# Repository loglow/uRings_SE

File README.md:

# µRings SE (uRings, microRings) Eurorack [Rev D]

## 8HP Eurorack module | Resonator

[μRings SE](http://urings-se.com) is a resonator, transforming unpitched external excitation signals into pitched sounds by modeling the vibrations of bars, tubes, and strings.

This re-engineered Eurorack module updates and simplifies the classic [Mutable Instruments Rings](https://mutable-instruments.net/modules/rings/) design by miniaturizing the module from 14HP to 8HP and redesigning the front panel layout without eliminating any original functionality.

Fully compatible with upstream Rings firmware. Includes power cable, mounting hardware, and a one-year warranty. Designed and built with care by [Tall Dog Electronics](http://tall-dog.com) in Western Massachusetts. Licensed [CC BY-SA 4.0](https://creativecommons.org/licenses/by-sa/4.0/) open source hardware.

- **Height:** 3U (128.5 mm)
- **Width:** 8HP (40.3 mm)
- **Depth:** 43 mm (with power)
- **+12V:** 120 mA (average)
- **-12V:** 5 mA (average)

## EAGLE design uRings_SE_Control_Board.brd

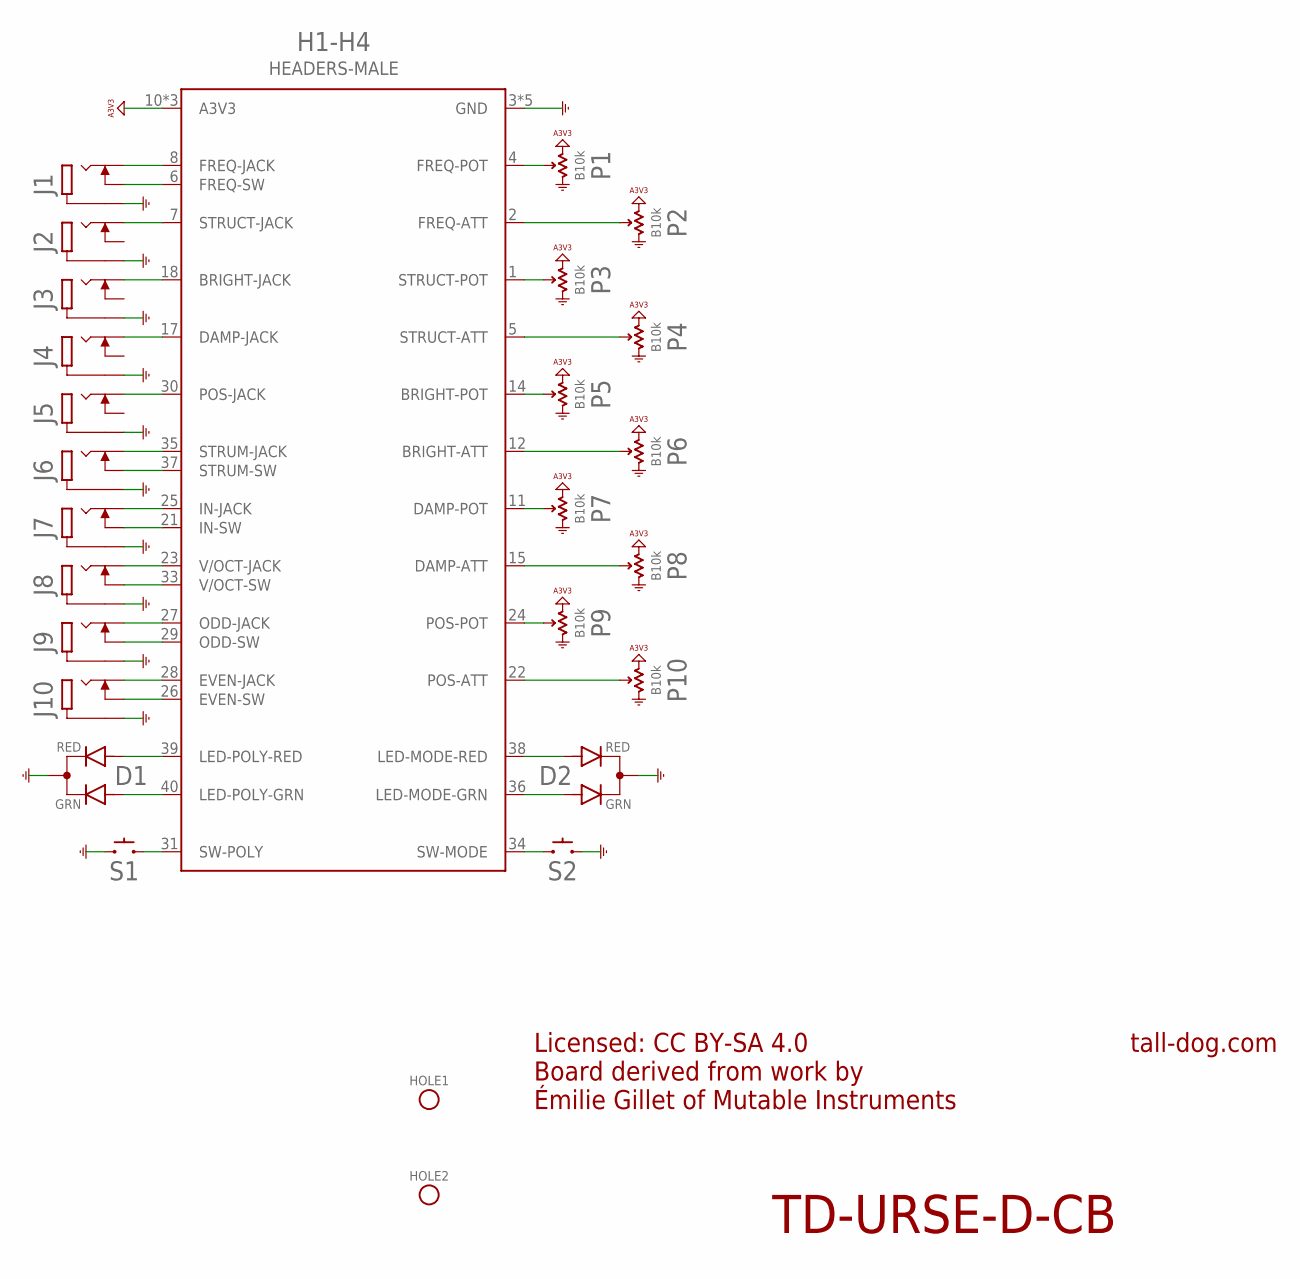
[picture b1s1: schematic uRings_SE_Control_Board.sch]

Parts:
D1, D2: LED-DUAL; LED-T1-3
H1-H4: HEADERS-MALE
HOLE1, HOLE2: HOLE; M2.5-HOLE
J1, J2, J3, J4, J5, J6, J7, J8, J9, J10: JACK
P1, P2, P3, P4, P5, P6, P7, P8, P9, P10: B10k; POT
S1, S2: SPST; TL1105

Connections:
A3V3: H1-H4.10 (A3V3), H1-H4.16 (A3V3), H1-H4.20 (A3V3), P1.P$1 (E), P2.P$1 (E), P3.P$1 (E), P4.P$1 (E), P5.P$1 (E), P6.P$1 (E), P7.P$1 (E), P8.P$1 (E), P9.P$1 (E), P10.P$1 (E)
BRIGHT-ATT: H1-H4.12 (BRIGHT-ATT), P6.P$2 (S)
BRIGHT-JACK: H1-H4.18 (BRIGHT-JACK), J3.P3 (3)
BRIGHT-POT: H1-H4.14 (BRIGHT-POT), P5.P$2 (S)
DAMP-ATT: H1-H4.15 (DAMP-ATT), P8.P$2 (S)
DAMP-JACK: H1-H4.17 (DAMP-JACK), J4.P3 (3)
DAMP-POT: H1-H4.11 (DAMP-POT), P7.P$2 (S)
EVEN-JACK: H1-H4.28 (EVEN-JACK), J10.P3 (3)
EVEN-SW: H1-H4.26 (EVEN-SW), J10.P2 (2)
FREQ-ATT: H1-H4.2 (FREQ-ATT), P2.P$2 (S)
FREQ-JACK: H1-H4.8 (FREQ-JACK), J1.P3 (3)
FREQ-POT: H1-H4.4 (FREQ-POT), P1.P$2 (S)
FREQ-SW: H1-H4.6 (FREQ-SW), J1.P2 (2)
GND: D1.2 (C), D2.2 (C), H1-H4.3 (GND), H1-H4.9 (GND), H1-H4.13 (GND), H1-H4.19 (GND), H1-H4.32 (GND), J1.P1 (1), J2.P1 (1), J3.P1 (1), J4.P1 (1), J5.P1 (1), J6.P1 (1), J7.P1 (1), J8.P1 (1), J9.P1 (1), J10.P1 (1), P1.P$3 (A), P2.P$3 (A), P3.P$3 (A), P4.P$3 (A), P5.P$3 (A), P6.P$3 (A), P7.P$3 (A), P8.P$3 (A), P9.P$3 (A), P10.P$3 (A), S1.1, S1.2 (1), S2.1, S2.2 (1)
IN-JACK: H1-H4.25 (IN-JACK), J7.P3 (3)
IN-SW: H1-H4.21 (IN-SW), J7.P2 (2)
LED-MODE-GRN: D2.3 (GRN), H1-H4.36 (LED-MODE-GRN)
LED-MODE-RED: D2.1 (RED), H1-H4.38 (LED-MODE-RED)
LED-POLY-GRN: D1.3 (GRN), H1-H4.40 (LED-POLY-GRN)
LED-POLY-RED: D1.1 (RED), H1-H4.39 (LED-POLY-RED)
ODD-JACK: H1-H4.27 (ODD-JACK), J9.P3 (3)
ODD-SW: H1-H4.29 (ODD-SW), J9.P2 (2)
POS-ATT: H1-H4.22 (POS-ATT), P10.P$2 (S)
POS-JACK: H1-H4.30 (POS-JACK), J5.P3 (3)
POS-POT: H1-H4.24 (POS-POT), P9.P$2 (S)
STRUCT-ATT: H1-H4.5 (STRUCT-ATT), P4.P$2 (S)
STRUCT-JACK: H1-H4.7 (STRUCT-JACK), J2.P3 (3)
STRUCT-POT: H1-H4.1 (STRUCT-POT), P3.P$2 (S)
STRUM-JACK: H1-H4.35 (STRUM-JACK), J6.P3 (3)
STRUM-SW: H1-H4.37 (STRUM-SW), J6.P2 (2)
SW-MODE: H1-H4.34 (SW-MODE), S2.3 (2), S2.4 (2)
SW-POLY: H1-H4.31 (SW-POLY), S1.3 (2), S1.4 (2)
V/OCT-JACK: H1-H4.23 (V/OCT-JACK), J8.P3 (3)
V/OCT-SW: H1-H4.33 (V/OCT-SW), J8.P2 (2)

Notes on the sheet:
Licensed: CC BY-SA 4.0 Board derived from work by Émilie Gillet of Mutable Instruments
tall-dog.com
TD-URSE-D-CB

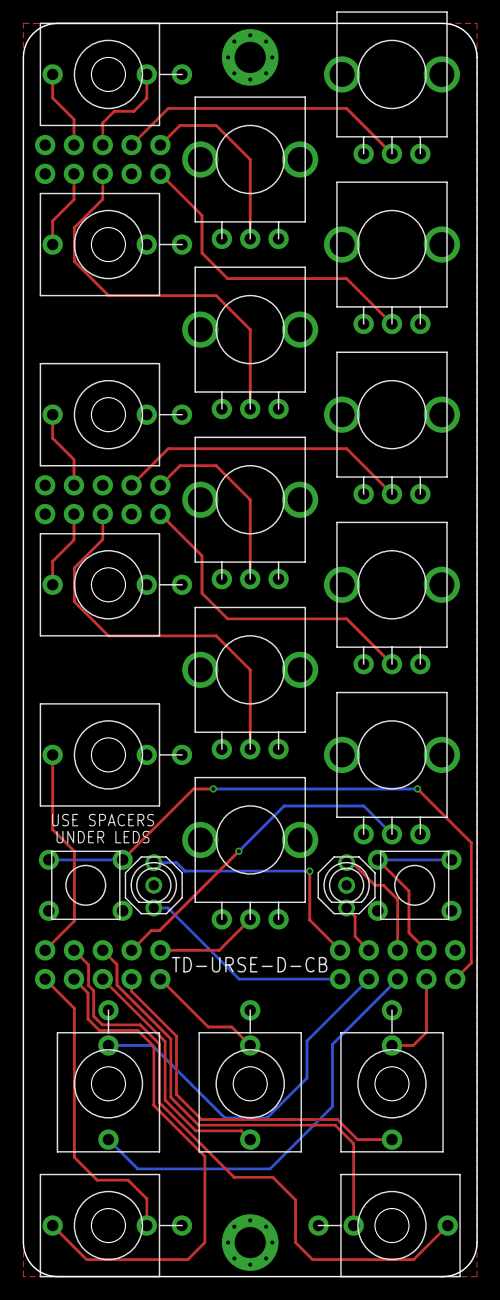
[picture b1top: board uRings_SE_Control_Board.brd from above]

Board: 2 copper layers, 40.0 x 110.5 mm, 29 parts (0 on the bottom side), 34 nets.

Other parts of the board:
U$1, U$2: LED-SPACER

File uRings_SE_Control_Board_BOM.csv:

Ref,Qty,Desc,Mfg,MPN
D1 D2,2,LED GRN/RED DIFF 3MM ROUND T/H,Kingbright,WP3VEGW
H1 H2 H3 H4,4,CONN HEADER 10POS .100 STR 15AU,Amphenol ICC (FCI),67997-210HLF
J1 J2 J3 J4 J5 J6 J7 J8 J9 J10,10,3.5MM JACK VERTICAL PCB MOUNT,Wenzhou QingPu,WQP-WQP518MA
P1 P3 P5 P7 P9,5,POT 9MM LINEAR B10K WHITE LINE,Song Huei,"R0904N-B10K,L-25KQ/LWS"
P2 P4 P6 P8 P10,5,POT 9MM LINEAR B10K WHITE LINE CENTER DETENT,Song Huei,"R0904N-B10K,L-25KQ/LWS/CC"
S1 S2,2,SWITCH TACTILE SPST-NO 0.05A 12V,E-Switch,TL1105DF160Q

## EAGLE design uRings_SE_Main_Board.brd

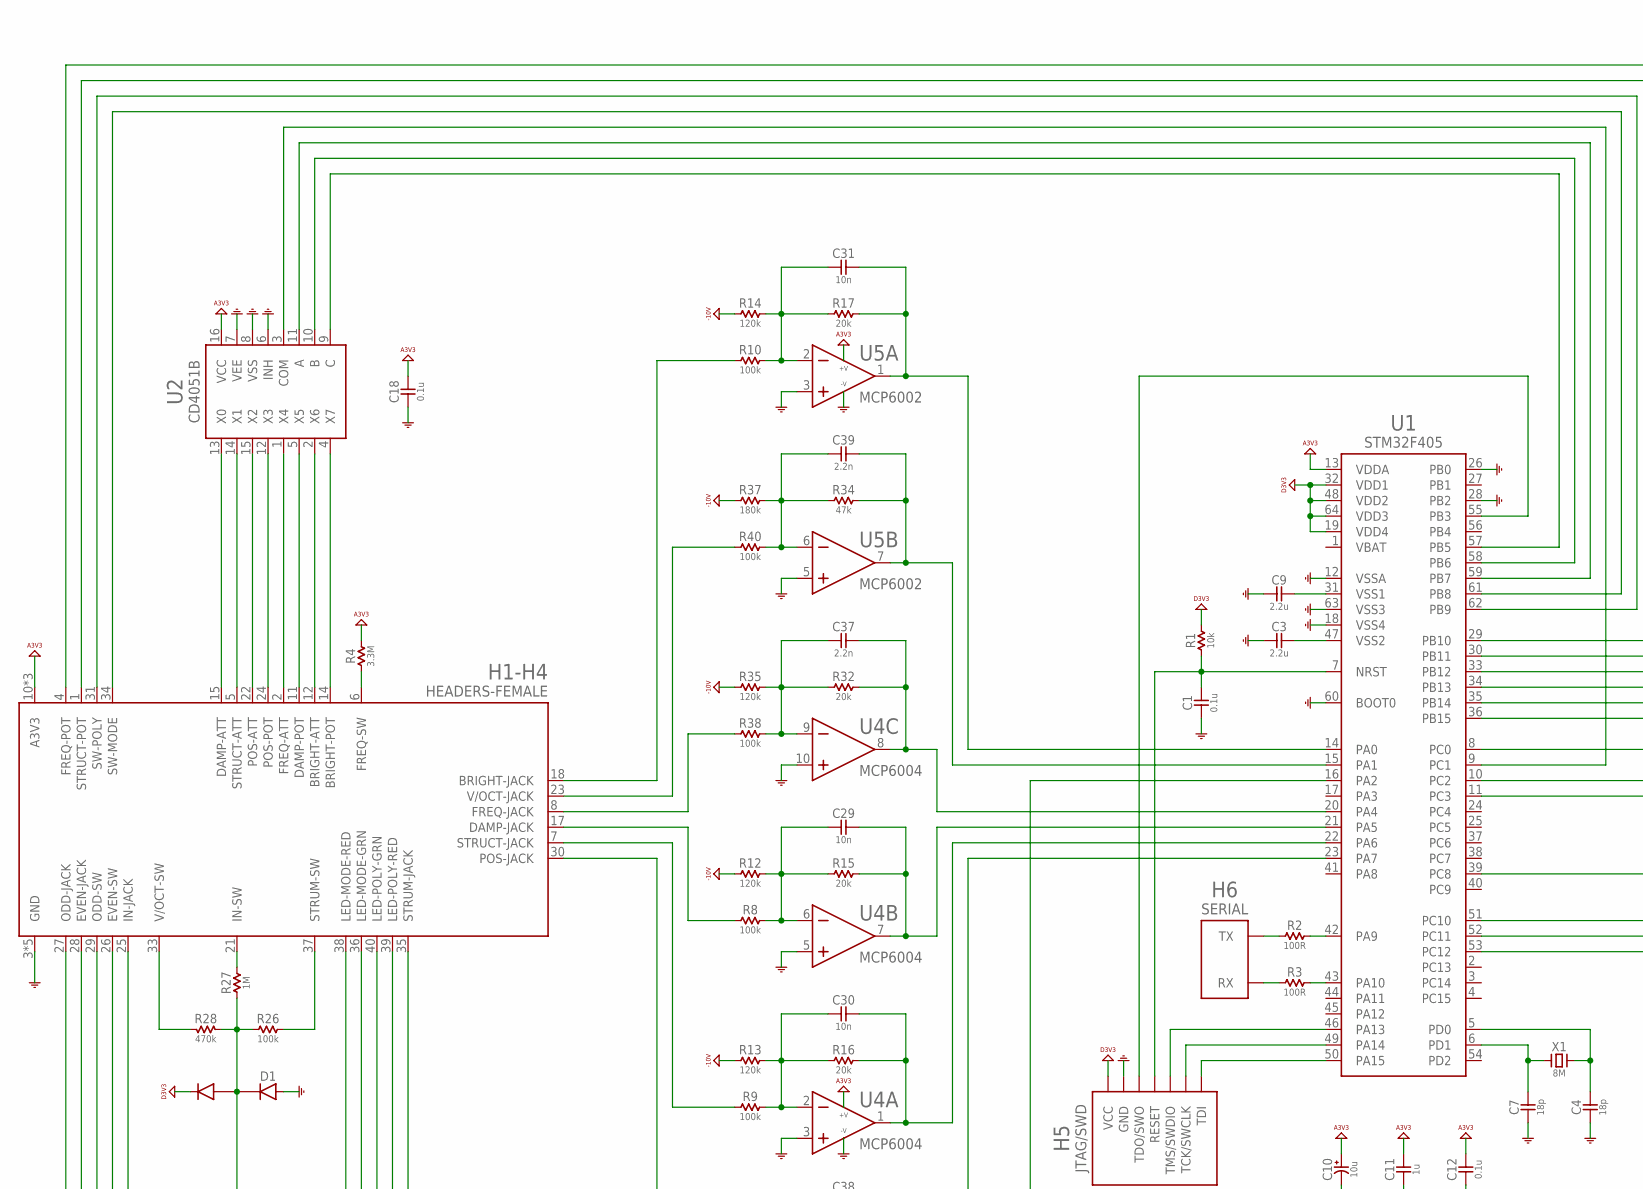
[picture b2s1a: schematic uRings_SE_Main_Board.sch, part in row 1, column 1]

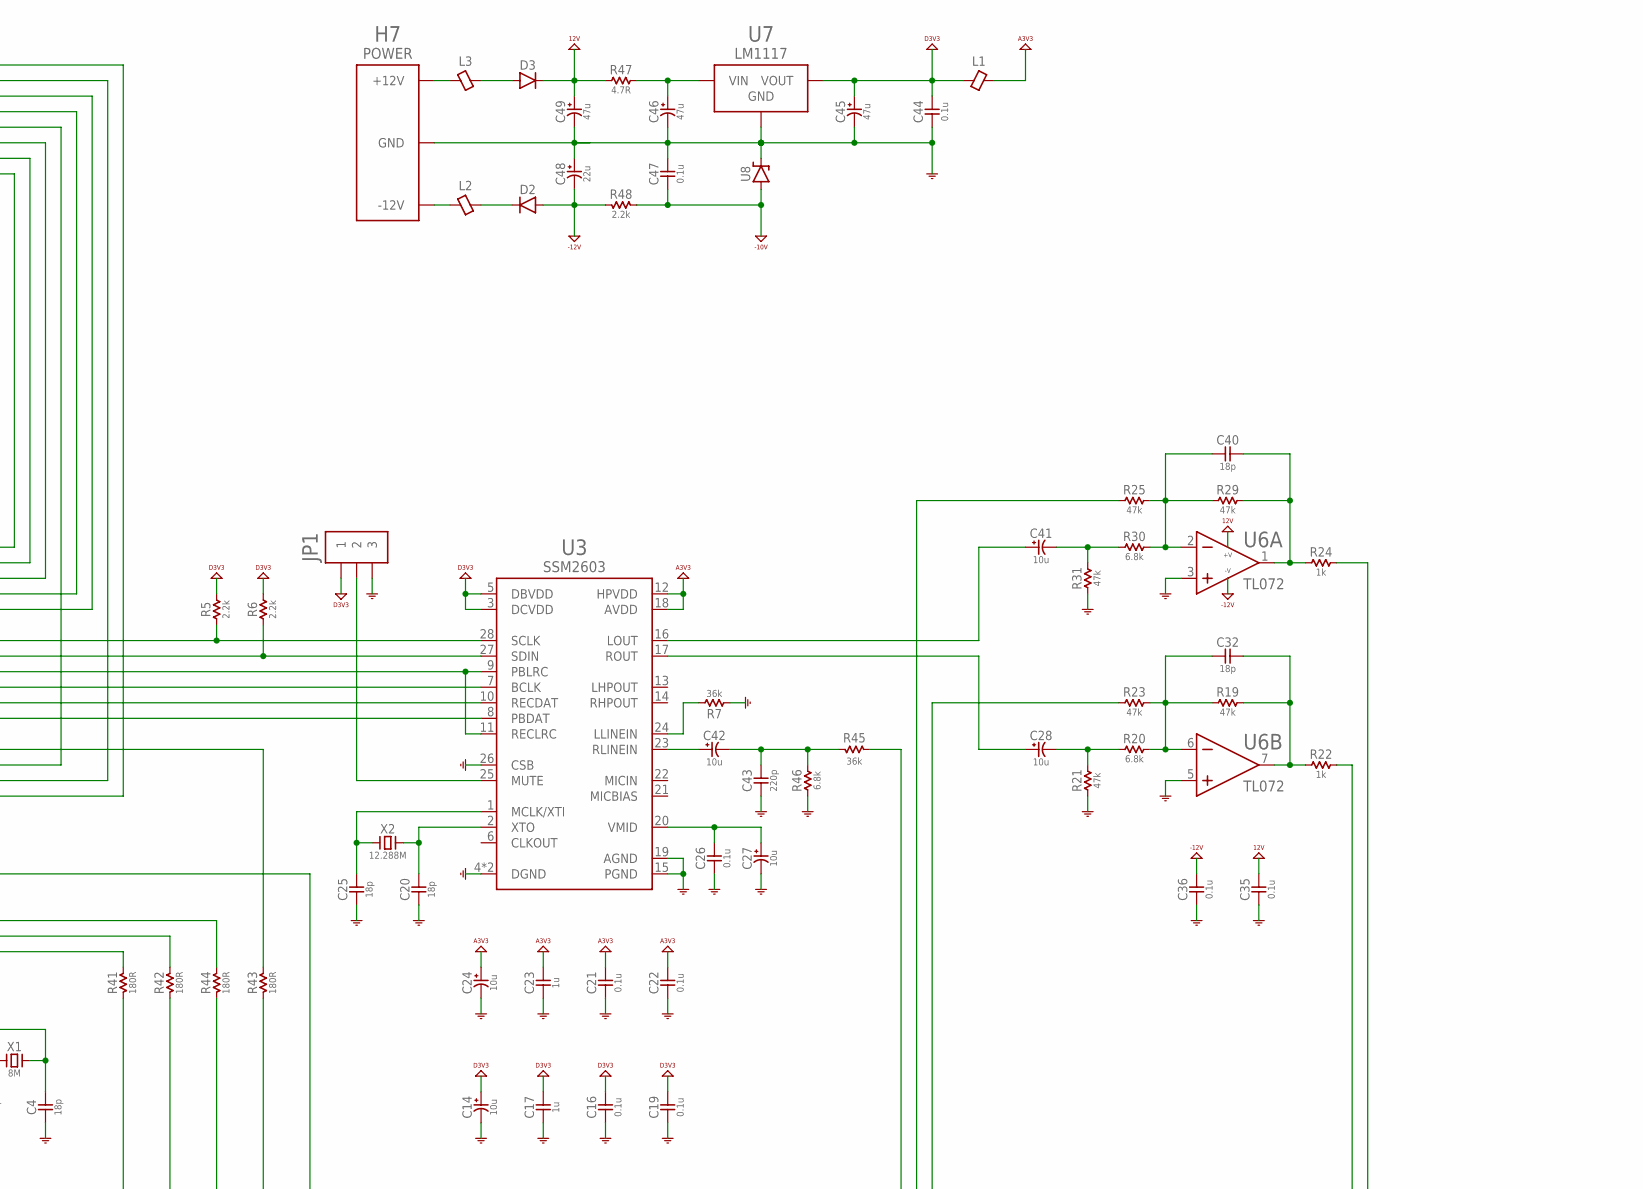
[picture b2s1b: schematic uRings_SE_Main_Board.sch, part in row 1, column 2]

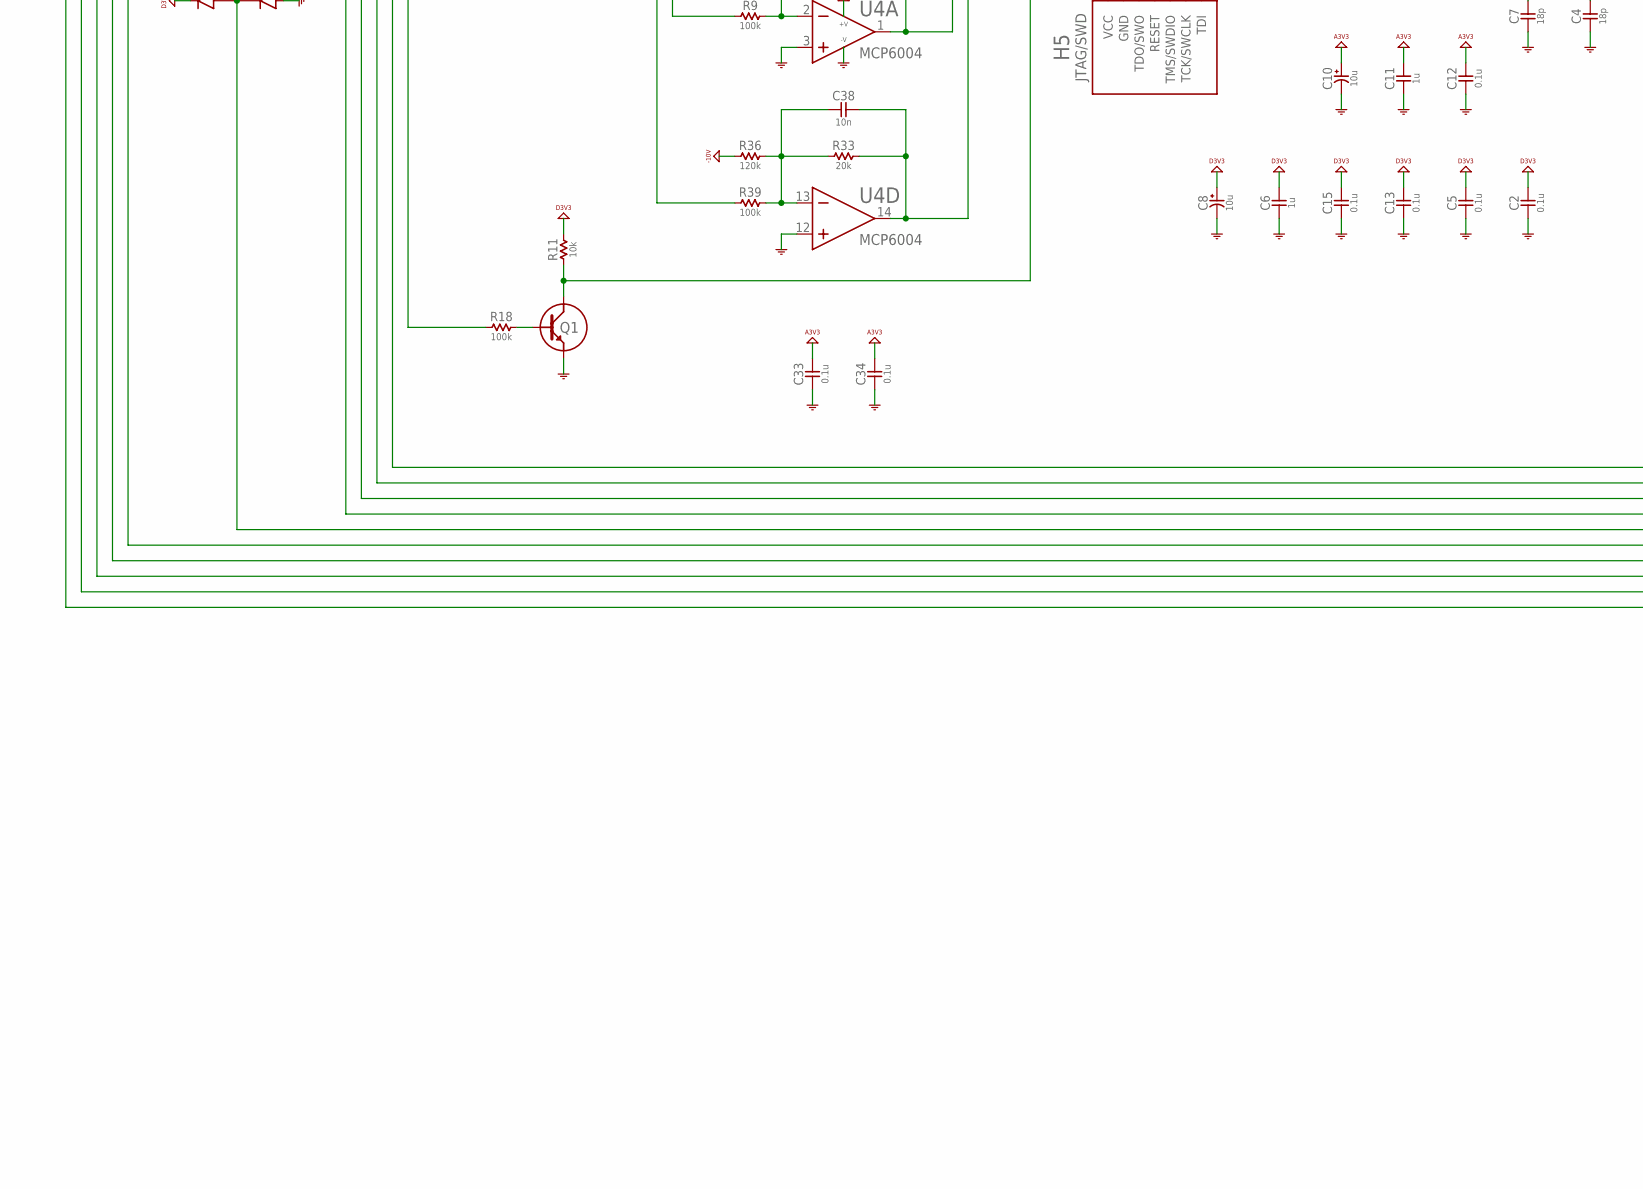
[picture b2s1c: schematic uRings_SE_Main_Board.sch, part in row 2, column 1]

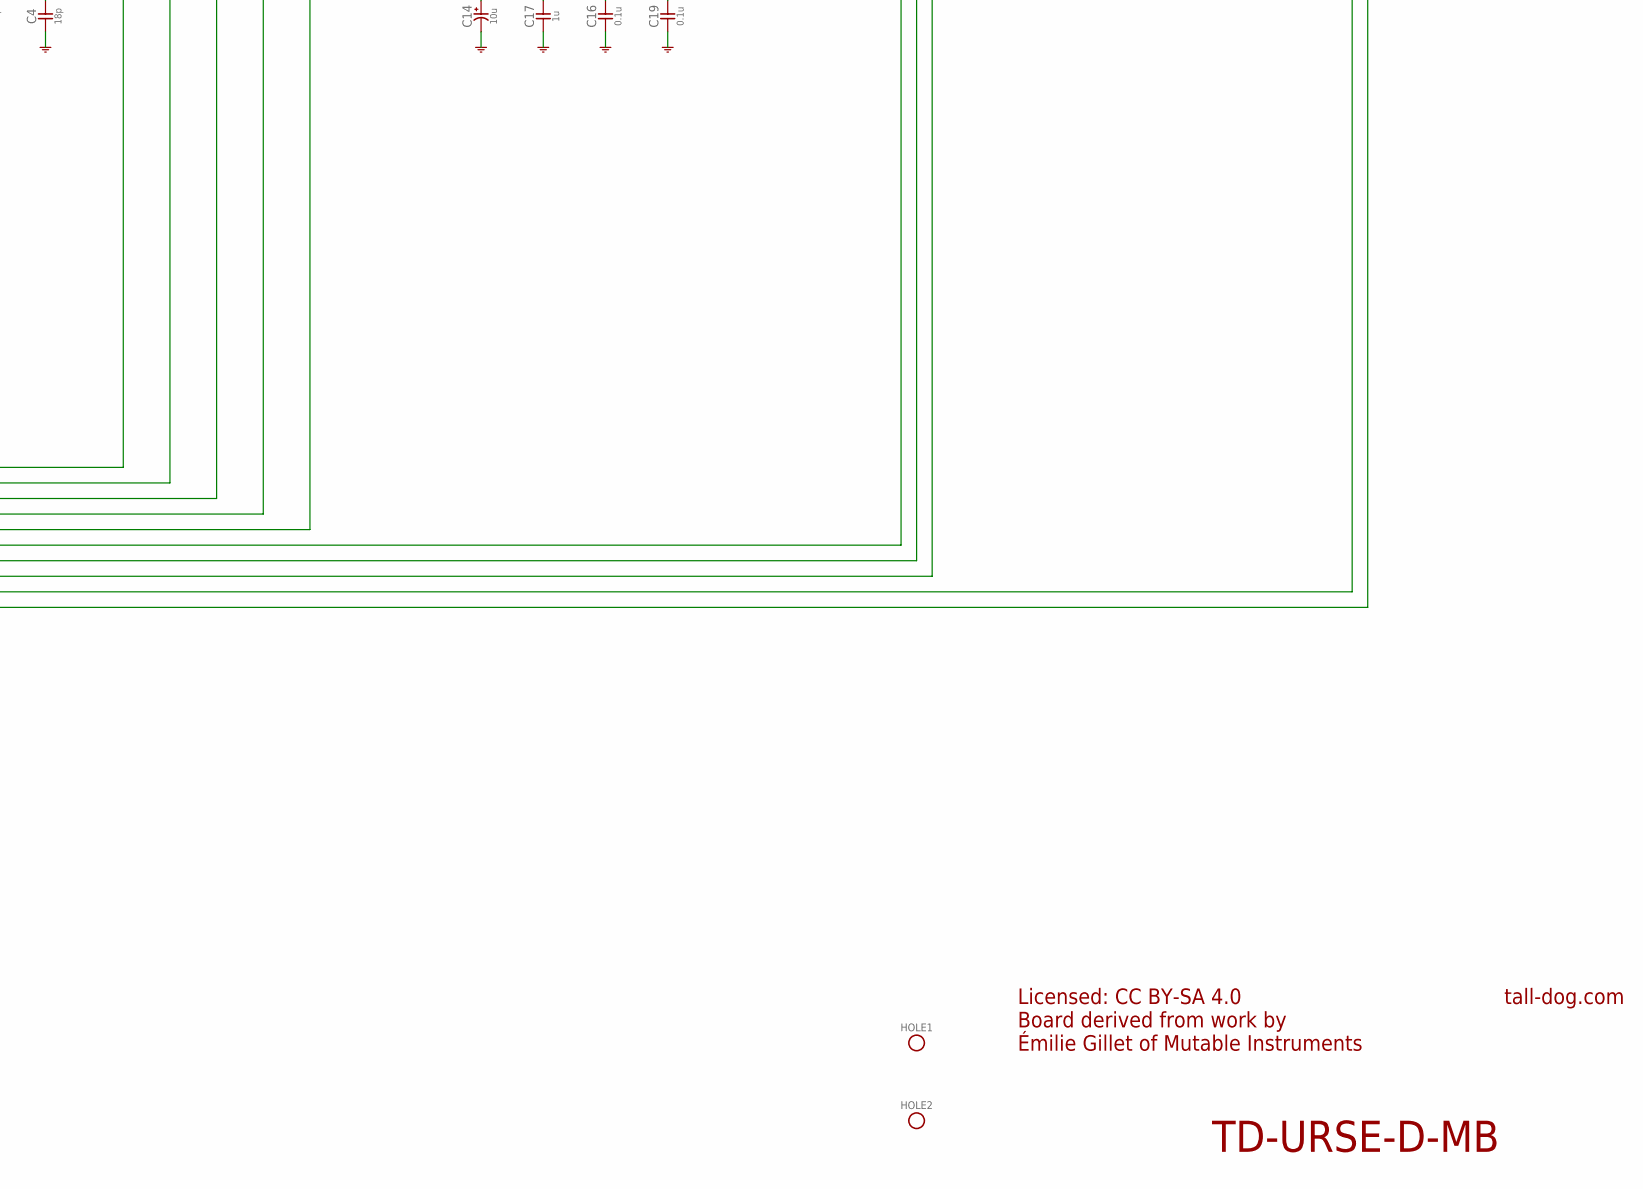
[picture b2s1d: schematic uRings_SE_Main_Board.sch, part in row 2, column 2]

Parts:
C1, C2, C5, C12, C13, C15, C16, C18, C19, C21, C22, C26, C33, C34, C35, C36, C44, C47: 0.1u; 0603-NP
C3, C9: 2.2u; 0603-NP
C4, C7, C20, C25, C32, C40: 18p; 0603-NP
C6, C11, C17, C23: 1u; 0603-NP
C8, C10, C14, C24, C27, C28, C41, C42: 10u; ELECTRO-SMD-4.3MM
C29, C30, C31, C38: 10n; 0603-NP
C37, C39: 2.2n; 0603-NP
C43: 220p; 0603-NP
C45, C46, C49: 47u; ELECTRO-SMD-6.6MM
C48: 22u; ELECTRO-SMD-6.6MM
D1: DIODE-DUAL; SOT-23
D2, D3: DIODE; SOD-123
H1-H4: HEADERS-FEMALE
H5: JTAG/SWD; PTH-0.05-2X5-SHROUDED
H6: SERIAL
H7: POWER; PTH-0.1-2X5-SHROUDED
HOLE1, HOLE2: HOLE; M2.5-HOLE
JP1: JUMPER-3
L1, L2, L3: FERRITE-BEAD-0603; 0603-NP
Q1: NPN; SOT-23
R1, R11: 10k; 0603-NP
R2, R3: 100R; 0603-NP
R4: 3.3M; 1206-NP
R5, R6, R48: 2.2k; 0603-NP
R7, R45: 36k; 0603-NP
R8, R9, R10, R18, R26, R38, R39, R40: 100k; 0603-NP
R12, R13, R14, R35, R36: 120k; 0603-NP
R15, R16, R17, R32, R33: 20k; 0603-NP
R19, R21, R23, R25, R29, R31, R34: 47k; 0603-NP
R20, R30, R46: 6.8k; 0603-NP
R22, R24: 1k; 0603-NP
R27: 1M; 1206-NP
R28: 470k; 1206-NP
R37: 180k; 0603-NP
R41, R42, R43, R44: 180R; 0603-NP
R47: 4.7R; 1206-NP
U1: STM32F405; LQFP-64
U2: CD4051B; TSSOP-16
U3: SSM2603; QFN-28
U4: MCP6004; TSSOP-14
U5: MCP6002; MSOP-8
U6: TL072; TSSOP-8
U7: LM1117; SOT-223
U8: ZENER; SOT-23
X1: 8M; CRYSTAL-ABM3
X2: 12.288M; CRYSTAL-ABM3

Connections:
12V: C35.2, C49.A (POS), D3.C, R47.1, U6.8 (POS)
-10V: C47.2, R12.1, R13.1, R14.1, R35.1, R36.1, R37.1, R48.1, U8.2 (A)
-12V: C36.1, C48.C (NEG), D2.A, R48.2, U6.4 (NEG)
A3V3: C10.A (POS), C11.2, C12.2, C18.2, C21.2, C22.2, C23.2, C24.A (POS), C33.2, C34.2, H1-H4.10 (A3V3), H1-H4.16 (A3V3), H1-H4.20 (A3V3), L1.2, R4.2, U1.13 (VDDA), U2.16 (VCC), U3.12 (HPVDD), U3.18 (AVDD), U4.4 (POS), U5.8 (POS)
BRIGHT-ATT: H1-H4.12 (BRIGHT-ATT), U2.2 (X6)
BRIGHT-CV: C31.2, R17.2, U1.14 (PA0), U5.1 (OUT)
BRIGHT-JACK: H1-H4.18 (BRIGHT-JACK), R10.1
BRIGHT-POT: H1-H4.14 (BRIGHT-POT), U2.4 (X7)
D3V3: C2.2, C5.2, C6.2, C8.A (POS), C13.2, C14.A (POS), C15.2, C16.2, C17.2, C19.2, C44.2, C45.A (POS), D1.2 (C2), H5.1 (VCC), JP1.1, L1.1, R1.2, R5.2, R6.2, R11.2, U1.19 (VDD4), U1.32 (VDD1), U1.48 (VDD2), U1.64 (VDD3), U3.3 (DCVDD), U3.5 (DBVDD), U7.2 (VOUT), U7.4 (VOUT)
DAMP-ATT: H1-H4.15 (DAMP-ATT), U2.13 (X0)
DAMP-CV: C29.2, R15.2, U1.21 (PA5), U4.7 (OUT)
DAMP-JACK: H1-H4.17 (DAMP-JACK), R8.1
DAMP-POT: H1-H4.11 (DAMP-POT), U2.5 (X5)
EVEN-JACK: H1-H4.28 (EVEN-JACK), R22.2
EVEN-OUT: C28.A (POS), U3.17 (ROUT)
EVEN-SW: H1-H4.26 (EVEN-SW), R25.1
FREQ-ATT: H1-H4.2 (FREQ-ATT), U2.1 (X4)
FREQ-CV: C37.2, R32.2, U1.20 (PA4), U4.8 (OUT)
FREQ-JACK: H1-H4.8 (FREQ-JACK), R38.1
FREQ-POT: H1-H4.4 (FREQ-POT), U1.11 (PC3)
GND: C1.1, C2.1, C3.1, C4.2, C5.1, C6.1, C7.2, C8.C (NEG), C9.1, C10.C (NEG), C11.1, C12.1, C13.1, C14.C (NEG), C15.1, C16.1, C17.1, C18.1, C19.1, C20.1, C21.1, C22.1, C23.1, C24.C (NEG), C25.1, C26.1, C27.C (NEG), C33.1, C34.1, C35.1, C36.2, C43.1, C44.1, C45.C (NEG), C46.C (NEG), C47.1, C48.A (POS), C49.C (NEG), D1.1 (A1), H1-H4.3 (GND), H1-H4.9 (GND), H1-H4.13 (GND), H1-H4.19 (GND), H1-H4.32 (GND), H5.3 (GND), H5.5 (GND), H5.9 (GND), H7.3 (GND), H7.4 (GND), H7.5 (GND), H7.6 (GND), H7.7 (GND), H7.8 (GND), JP1.3, Q1.2 (E), R7.1, R21.1, R31.1, R46.1, U1.12 (VSSA), U1.18 (VSS4), U1.26 (PB0), U1.28 (PB2), U1.60 (BOOT0), U1.63 (VSS3), U2.6 (INH), U2.7 (VEE), U2.8 (VSS), U3.4 (DGND), U3.15 (PGND), U3.19 (AGND), U3.26 (CSB), U3.29 (DGND), U4.3 (IN+), U4.5 (+), U4.10 (+), U4.11 (NEG), U4.12 (+), U5.3 (IN+), U5.4 (NEG), U5.5 (+), U6.3 (IN+), U6.5 (+), U7.1 (GND), U8.1 (C)
I2C-SCL: R5.1, U1.29 (PB10), U3.28 (SCLK)
I2C-SDA: R6.1, U1.30 (PB11), U3.27 (SDIN)
I2S-LRCK: U1.33 (PB12), U3.9 (PBLRC), U3.11 (RECLRC)
I2S-SCK: U1.34 (PB13), U3.7 (BCLK)
I2S-SIN: U1.35 (PB14), U3.10 (RECDAT)
I2S-SOUT: U1.36 (PB15), U3.8 (PBDAT)
IN: C42.A (POS), U3.23 (RLINEIN)
IN-JACK: H1-H4.25 (IN-JACK), R45.1
IN-SW: H1-H4.21 (IN-SW), R27.2
JTCK/SWCLK: H5.4 (TCK/SWCLK), U1.49 (PA14)
JTDI: H5.8 (TDI), U1.50 (PA15)
JTDO/SWO: H5.6 (TDO/SWO), U1.55 (PB3)
JTMS/SWDIO: H5.2 (TMS/SWDIO), U1.46 (PA13)
LED-MODE-GRN: H1-H4.36 (LED-MODE-GRN), R44.2
LED-MODE-RED: H1-H4.38 (LED-MODE-RED), R43.2
LED-POLY-GRN: H1-H4.40 (LED-POLY-GRN), R42.2
LED-POLY-RED: H1-H4.39 (LED-POLY-RED), R41.2
MUTE: JP1.2, U3.25 (MUTE)
MUX-ADDR-0: U1.59 (PB7), U2.11 (A)
MUX-ADDR-1: U1.58 (PB6), U2.10 (B)
MUX-ADDR-2: U1.57 (PB5), U2.9 (C)
MUXED-POTS: U1.9 (PC1), U2.3 (COM)
unnamed: R43.1, U1.8 (PC0)
unnamed: C46.A (POS), R47.2, U7.3 (VIN)
unnamed: D3.A, L3.1
unnamed: D2.C, L2.1
unnamed: C29.1, R8.2, R12.2, R15.1, U4.6 (-)
unnamed: R44.1, U1.51 (PC10)
unnamed: C9.2, U1.31 (VSS1)
unnamed: C3.2, U1.47 (VSS2)
unnamed: R42.1, U1.52 (PC11)
unnamed: R41.1, U1.53 (PC12)
unnamed: C4.1, U1.5 (PD0), X1.2
unnamed: C7.1, U1.6 (PD1), X1.1
unnamed: C31.1, R10.2, R14.2, R17.1, U5.2 (IN-)
unnamed: C39.1, R34.1, R37.2, R40.2, U5.6 (-)
unnamed: C37.1, R32.1, R35.2, R38.2, U4.9 (-)
unnamed: C30.1, R9.2, R13.2, R16.1, U4.2 (IN-)
unnamed: C38.1, R33.1, R36.2, R39.2, U4.13 (-)
unnamed: C28.C (NEG), R20.1, R21.2
unnamed: C42.C (NEG), C43.2, R45.2, R46.2
unnamed: C41.C (NEG), R30.1, R31.2
unnamed: Q1.1 (B), R18.2
unnamed: C25.2, U3.1 (MCLK/XTI), X2.2
unnamed: C20.2, U3.2 (XTO), X2.1
unnamed: C32.1, R19.1, R20.2, R23.2, U6.6 (-)
unnamed: C32.2, R19.2, R22.1, U6.7 (OUT)
unnamed: C40.1, R25.2, R29.1, R30.2, U6.2 (IN-)
unnamed: C26.2, C27.A (POS), U3.20 (VMID)
unnamed: R7.2, U3.24 (LLINEIN)
unnamed: C40.2, R24.1, R29.2, U6.1 (OUT)
unnamed: H1-H4.6 (FREQ-SW), R4.1
unnamed: H7.1 (-12V), H7.2 (-12V), L2.2
unnamed: H7.9 (+12V), H7.10 (+12V), L3.2
NORM-PROBE: D1.3 (C1/A2), R26.1, R27.1, R28.1, U1.39 (PC8)
ODD-JACK: H1-H4.27 (ODD-JACK), R24.2
ODD-OUT: C41.A (POS), U3.16 (LOUT)
ODD-SW: H1-H4.29 (ODD-SW), R23.1
POS-ATT: H1-H4.22 (POS-ATT), U2.15 (X2)
POS-CV: C38.2, R33.2, U1.23 (PA7), U4.14 (OUT)
POS-JACK: H1-H4.30 (POS-JACK), R39.1
POS-POT: H1-H4.24 (POS-POT), U2.12 (X3)
RESET: C1.2, H5.10 (RESET), R1.1, U1.7 (NRST)
RX: H6.RX, R3.1
RX1: R3.2, U1.43 (PA10)
STRUCT-ATT: H1-H4.5 (STRUCT-ATT), U2.14 (X1)
STRUCT-CV: C30.2, R16.2, U1.22 (PA6), U4.1 (OUT)
STRUCT-JACK: H1-H4.7 (STRUCT-JACK), R9.1
STRUCT-POT: H1-H4.1 (STRUCT-POT), U1.10 (PC2)
STRUM: Q1.3 (C), R11.1, U1.16 (PA2)
STRUM-JACK: H1-H4.35 (STRUM-JACK), R18.1
STRUM-SW: H1-H4.37 (STRUM-SW), R26.2
SW-MODE: H1-H4.34 (SW-MODE), U1.61 (PB8)
SW-POLY: H1-H4.31 (SW-POLY), U1.62 (PB9)
TX: H6.TX, R2.1
TX1: R2.2, U1.42 (PA9)
V/OCT-CV: C39.2, R34.2, U1.15 (PA1), U5.7 (OUT)
V/OCT-JACK: H1-H4.23 (V/OCT-JACK), R40.1
V/OCT-SW: H1-H4.33 (V/OCT-SW), R28.2

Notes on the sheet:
Licensed: CC BY-SA 4.0 Board derived from work by Émilie Gillet of Mutable Instruments
tall-dog.com
TD-URSE-D-MB

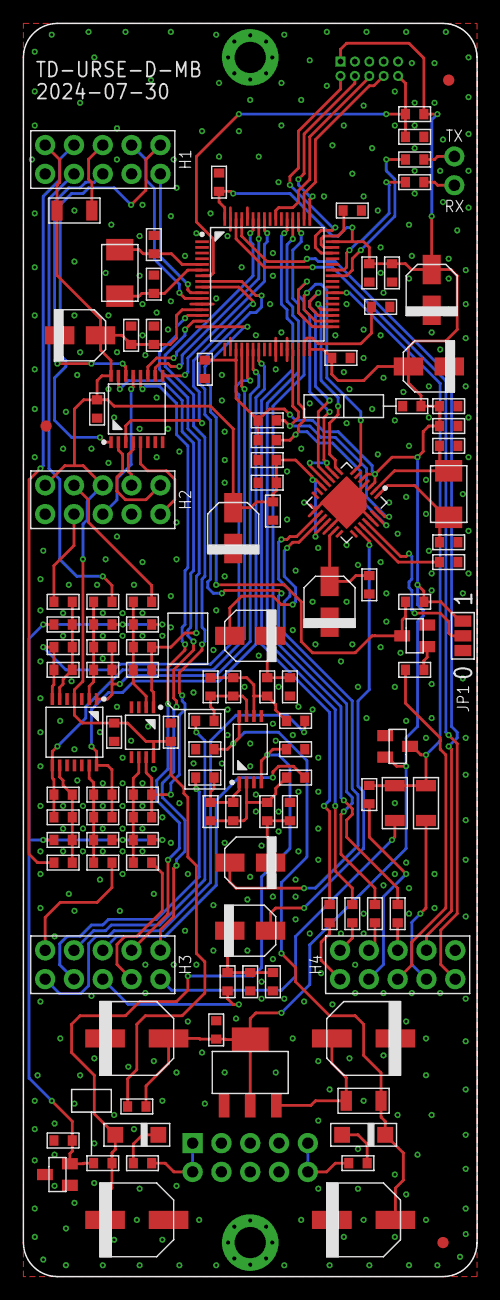
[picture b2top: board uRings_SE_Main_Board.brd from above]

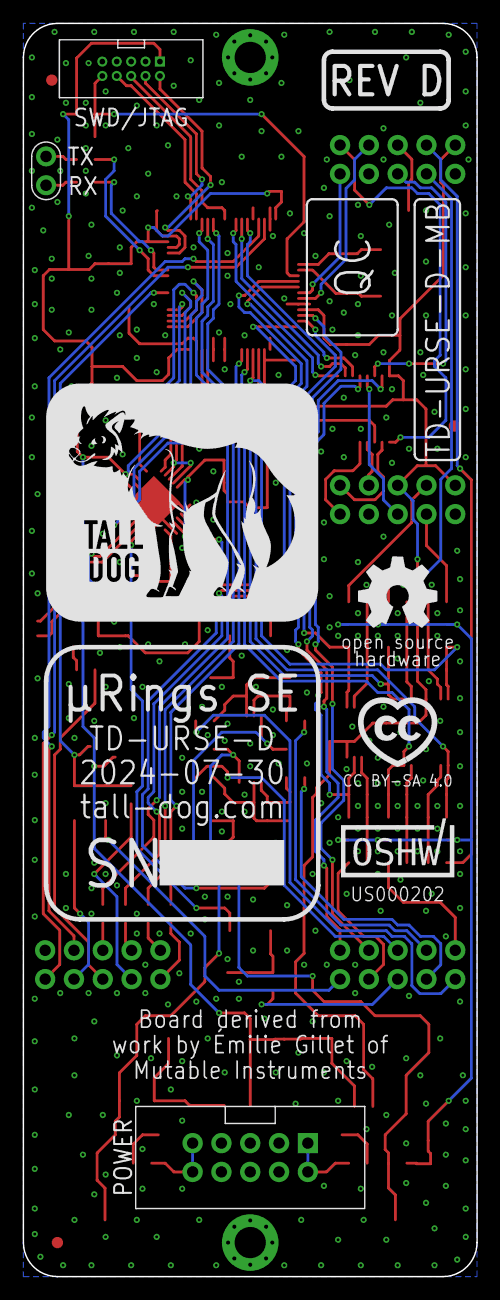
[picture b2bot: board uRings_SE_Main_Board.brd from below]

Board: 2 copper layers, 40.0 x 110.5 mm, 132 parts (11 on the bottom side), 100 nets.

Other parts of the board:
U$1: LOGO-PN
U$2, U$5, U$6: FIDUCIAL
U$3: LOGO-CC
U$4: LOGO-OSH
U$7: LOGO-SN
U$8: LOGO-OSHW
U$9: LOGO-TD
U$10: LOGO-REV
U$11: LOGO-QC

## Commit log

2018-11-17 initial commit, revision B production
2019-12-16 Updates for Revision C
2019-12-18 Cleanup and silkscreen artwork updates
2021-03-23 Revision C
2024-07-24 updates in preparation for rev D production
2024-08-08 revision D updates continued
